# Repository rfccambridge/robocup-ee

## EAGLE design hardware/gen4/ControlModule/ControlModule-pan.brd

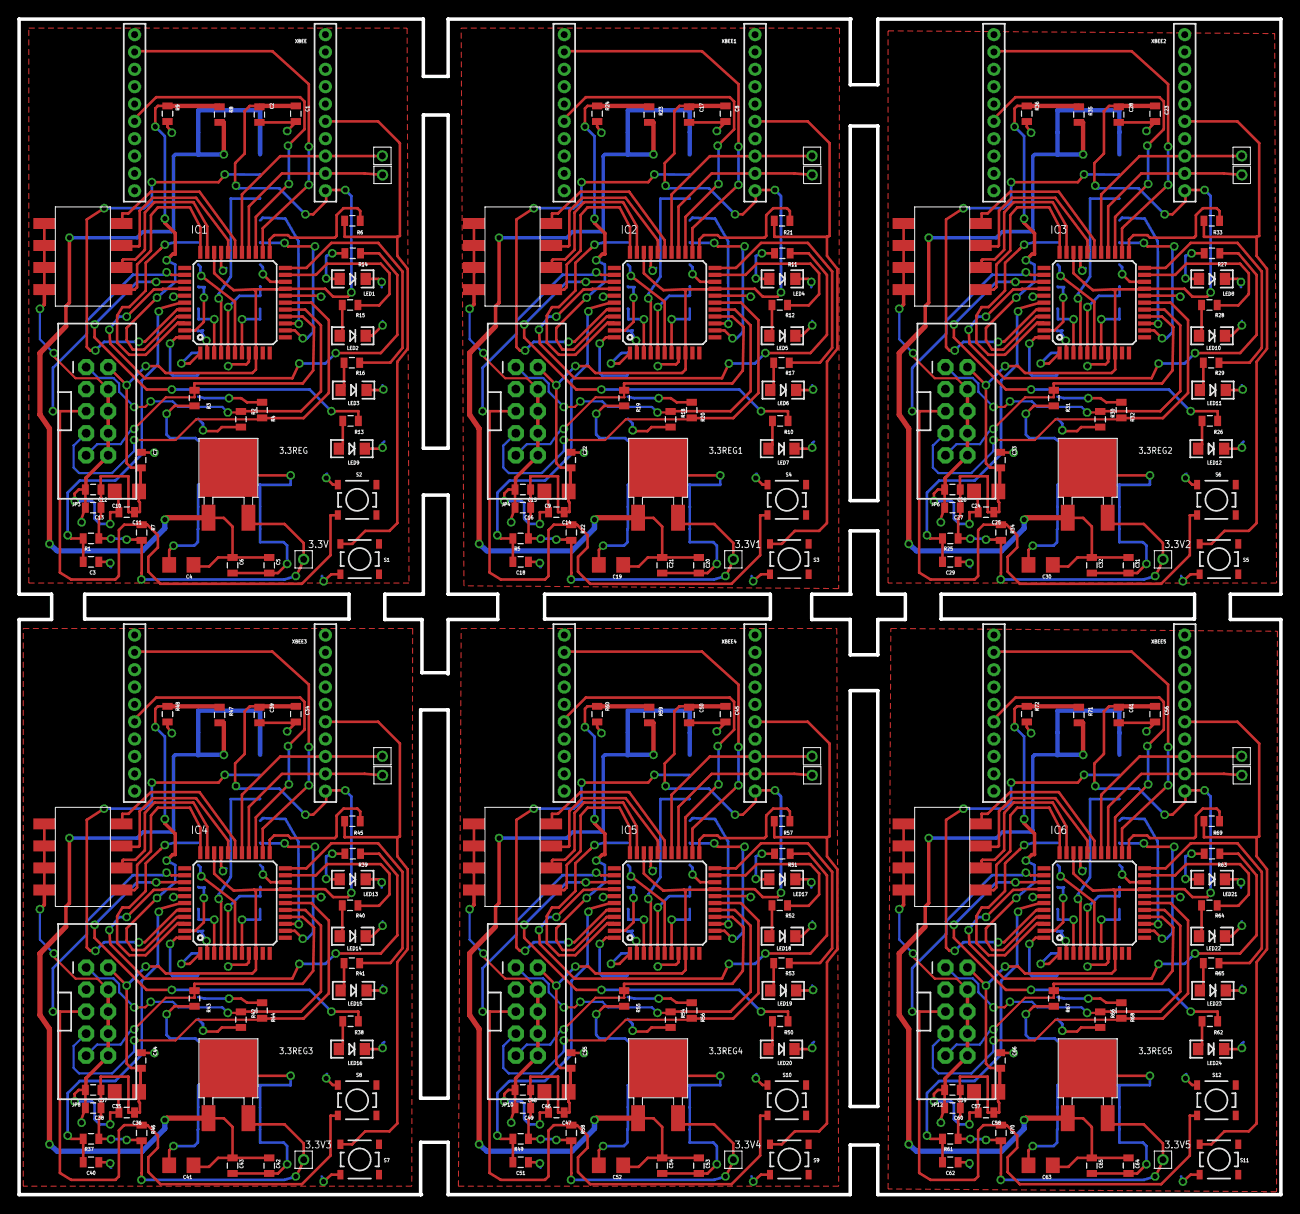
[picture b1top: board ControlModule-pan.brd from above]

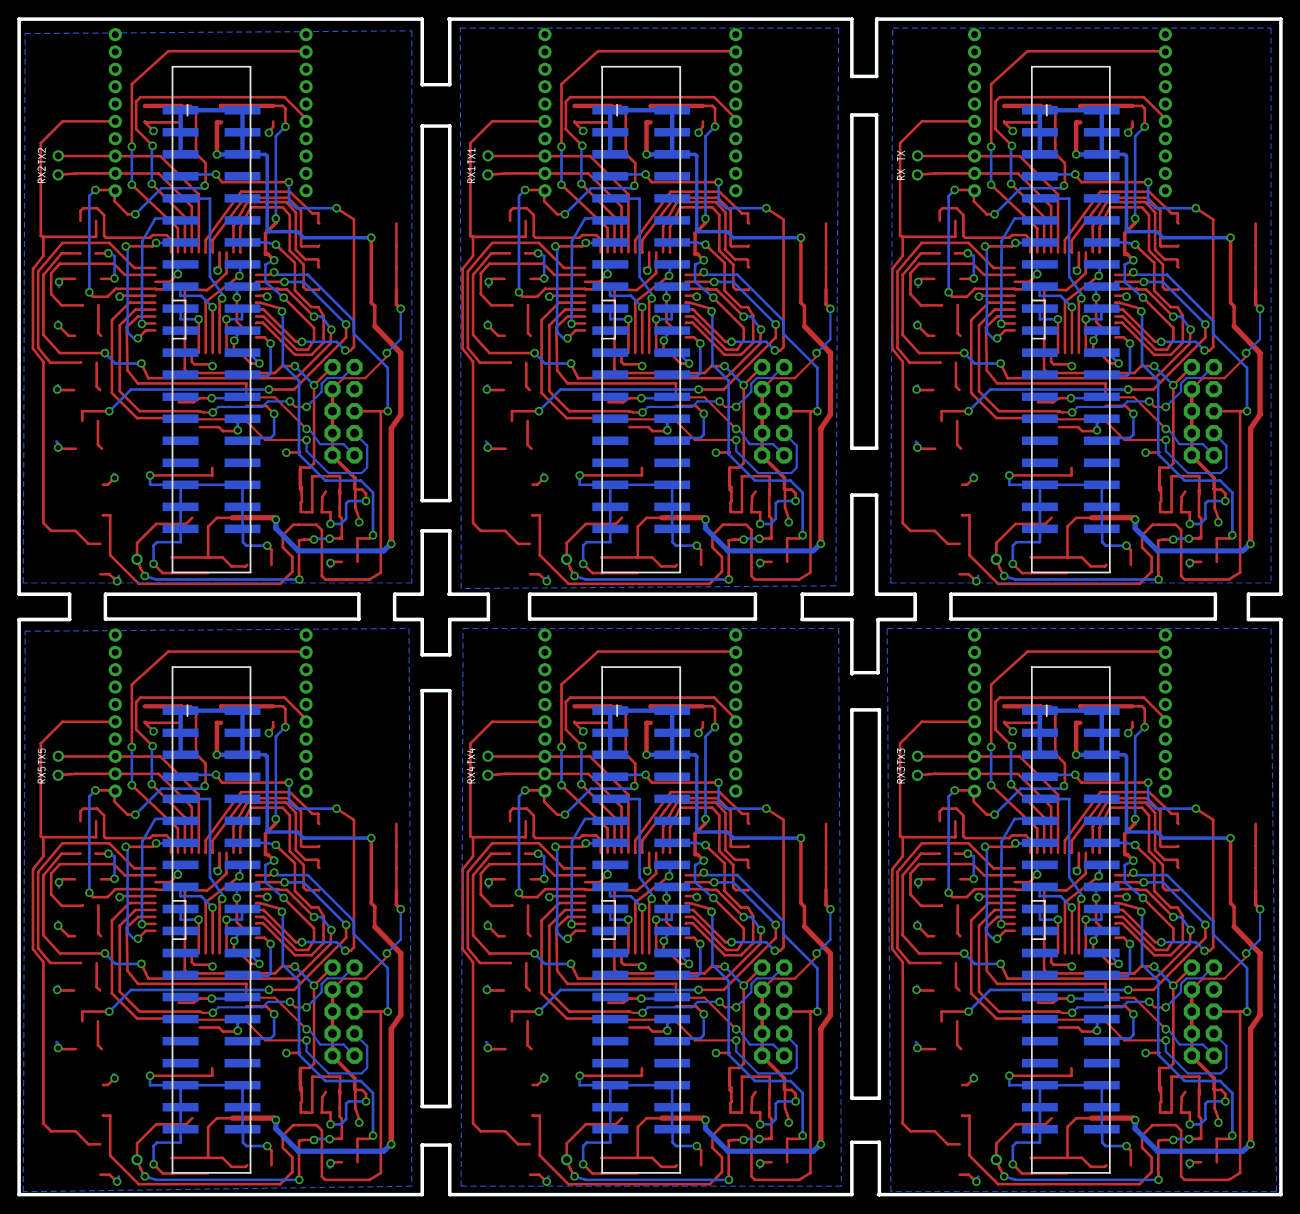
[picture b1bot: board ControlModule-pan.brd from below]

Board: 2 copper layers, 145.5 x 135.5 mm, 229 parts (6 on the bottom side), 270 nets.

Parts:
3.3REG, 3.3REG1, 3.3REG2, 3.3REG3, 3.3REG4, 3.3REG5: 3.3REG1AREG; DPAK
3.3V, 3.3V1, 3.3V2, 3.3V3, 3.3V4, 3.3V5: TEST_PT; TESTING_PT
C1, C5, C8, C12, C13, C15, C16, C20, C23, C26, C27, C31, C34, C37, C38, C42, C45, C48, C49, C53, C56, C59, C60, C64: 1uF; 0805
C2, C17, C28, C39, C50, C61: 0.01uF; 0805
C3, C18, C29, C40, C51, C62: 0.1uF; 0805
C4, C9, C10, C19, C24, C30, C35, C41, C46, C52, C57, C63: 47uF; 1206
C6, C7, C11, C14, C21, C22, C25, C32, C33, C36, C43, C44, C47, C54, C55, C58, C65, C66: .01uF; 0805
FRAME1: FRAME-LETTER; CREATIVE_COMMONS
IC1, IC2, IC3, IC4, IC5, IC6: XMEGA16A4A; TQFP44
JP1, JP2, JP5, JP7, JP9, JP11: M20X2SHROUDED_SMT; 2X20_SHROUDED_SMT
JP3, JP4, JP6, JP8, JP10, JP12: 2X5-SHROUDED
LED1, LED2, LED3, LED4, LED5, LED6, LED7, LED8, LED9, LED10, LED11, LED12, LED13, LED14, LED15, LED16, LED17, LED18, LED19, LED20, LED21, LED22, LED23, LED24: LED-1206
R1, R5, R7, R22, R25, R34, R37, R46, R49, R58, R61, R70: 10k; 0805
R2, R3, R4, R6, R18, R19, R20, R21, R30, R31, R32, R33, R42, R43, R44, R45, R54, R55, R56, R57, R66, R67, R68, R69: 4.7k; 0805
R8, R23, R35, R47, R59, R71: 80k; 0805
R9, R24, R36, R48, R60, R72: 20k; 0805
R10, R11, R12, R13, R14, R15, R16, R17, R26, R27, R28, R29, R38, R39, R40, R41, R50, R51, R52, R53, R62, R63, R64, R65: 1k; 0805
RX, RX1, RX2, RX3, RX4, RX5: TEST_PT; TESTING_PT
S1, S2, S3, S4, S5, S6, S7, S8, S9, S10, S11, S12: SWITCH-MOMENTARY-2SMD-2; TACTILE_SWITCH_SMD-2
TX, TX1, TX2, TX3, TX4, TX5: TEST_PT; TESTING_PT
U$1, U$2, U$3, U$4, U$5, U$6: 4-POS-DIP; 4-POS-DIP-SMD
XBEE, XBEE1, XBEE2, XBEE3, XBEE4, XBEE5: XBEE-1B1; XBEE-1

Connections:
3.3V: 3.3REG.SOURCE, 3.3V.P$1, C1.1, C2.1, C7.1, C10.1, C11.2, C12.2, C13.1, IC1.9, IC1.19, IC1.31, JP3.2, R1.2, R7.2, XBEE.1
3.3V1: 3.3REG1.SOURCE, 3.3V1.P$1, C8.1, C9.1, C14.2, C15.2, C16.1, C17.1, C22.1, IC2.9, IC2.19, IC2.31, JP4.2, R5.2, R22.2, XBEE1.1
3.3V2: 3.3REG2.SOURCE, 3.3V2.P$1, C23.1, C24.1, C25.2, C26.2, C27.1, C28.1, C33.1, IC3.9, IC3.19, IC3.31, JP6.2, R25.2, R34.2, XBEE2.1
3.3V3: 3.3REG3.SOURCE, 3.3V3.P$1, C34.1, C35.1, C36.2, C37.2, C38.1, C39.1, C44.1, IC4.9, IC4.19, IC4.31, JP8.2, R37.2, R46.2, XBEE3.1
3.3V4: 3.3REG4.SOURCE, 3.3V4.P$1, C45.1, C46.1, C47.2, C48.2, C49.1, C50.1, C55.1, IC5.9, IC5.19, IC5.31, JP10.2, R49.2, R58.2, XBEE4.1
3.3V5: 3.3REG5.SOURCE, 3.3V5.P$1, C56.1, C57.1, C58.2, C59.2, C60.1, C61.1, C66.1, IC6.9, IC6.19, IC6.31, JP12.2, R61.2, R70.2, XBEE5.1
12V: 3.3REG.GATE, C4.1, C5.1, C6.1, JP1.1, JP1.2, JP1.3, JP1.4, JP1.5, JP1.6, R8.2
12V1: 3.3REG1.GATE, C19.1, C20.1, C21.1, JP2.1, JP2.2, JP2.3, JP2.4, JP2.5, JP2.6, R23.2
12V2: 3.3REG2.GATE, C30.1, C31.1, C32.1, JP5.1, JP5.2, JP5.3, JP5.4, JP5.5, JP5.6, R35.2
12V3: 3.3REG3.GATE, C41.1, C42.1, C43.1, JP7.1, JP7.2, JP7.3, JP7.4, JP7.5, JP7.6, R47.2
12V4: 3.3REG4.GATE, C52.1, C53.1, C54.1, JP9.1, JP9.2, JP9.3, JP9.4, JP9.5, JP9.6, R59.2
12V5: 3.3REG5.GATE, C63.1, C64.1, C65.1, JP11.1, JP11.2, JP11.3, JP11.4, JP11.5, JP11.6, R71.2
12VGND: 3.3REG.DRAIN, C4.2, C5.2, C6.2, JP1.35, JP1.36, JP1.37, JP1.38, JP1.39, JP1.40
12VGND1: 3.3REG1.DRAIN, C19.2, C20.2, C21.2, JP2.35, JP2.36, JP2.37, JP2.38, JP2.39, JP2.40
12VGND2: 3.3REG2.DRAIN, C30.2, C31.2, C32.2, JP5.35, JP5.36, JP5.37, JP5.38, JP5.39, JP5.40
12VGND3: 3.3REG3.DRAIN, C41.2, C42.2, C43.2, JP7.35, JP7.36, JP7.37, JP7.38, JP7.39, JP7.40
12VGND4: 3.3REG4.DRAIN, C52.2, C53.2, C54.2, JP9.35, JP9.36, JP9.37, JP9.38, JP9.39, JP9.40
12VGND5: 3.3REG5.DRAIN, C63.2, C64.2, C65.2, JP11.35, JP11.36, JP11.37, JP11.38, JP11.39, JP11.40
BATSENSE: IC1.41, R8.1, R9.2
BATSENSE1: IC2.41, R23.1, R24.2
BATSENSE2: IC3.41, R35.1, R36.2
BATSENSE3: IC4.41, R47.1, R48.2
BATSENSE4: IC5.41, R59.1, R60.2
BATSENSE5: IC6.41, R71.1, R72.2
BB_IN: IC1.40, JP1.7
BB_IN1: IC2.40, JP2.7
BB_IN2: IC3.40, JP5.7
BB_IN3: IC4.40, JP7.7
BB_IN4: IC5.40, JP9.7
BB_IN5: IC6.40, JP11.7
BB_OUT: IC1.4, JP1.9
BB_OUT1: IC2.4, JP2.9
BB_OUT2: IC3.4, JP5.9
BB_OUT3: IC4.4, JP7.9
BB_OUT4: IC5.4, JP9.9
BB_OUT5: IC6.4, JP11.9
BID0: IC1.28, U$1.1
BID1: IC1.29, U$1.2
BID2: IC1.32, U$1.3
BID3: IC1.33, U$1.4
BID4: IC2.28, U$2.1
BID5: IC2.32, U$2.3
BID6: IC2.29, U$2.2
BID7: IC2.33, U$2.4
BID8: IC3.28, U$3.1
BID9: IC3.32, U$3.3
BID10: IC3.29, U$3.2
BID11: IC3.33, U$3.4
BID12: IC4.28, U$4.1
BID13: IC4.32, U$4.3
BID14: IC4.29, U$4.2
BID15: IC4.33, U$4.4
BID16: IC5.28, U$5.1
BID17: IC5.32, U$5.3
BID18: IC5.29, U$5.2
BID19: IC5.33, U$5.4
BID20: IC6.28, U$6.1
BID21: IC6.32, U$6.3
BID22: IC6.29, U$6.2
BID23: IC6.33, U$6.4
CHARGE: IC1.7, JP1.19
CHARGE1: IC2.7, JP2.19
CHARGE2: IC3.7, JP5.19
CHARGE3: IC4.7, JP7.19
CHARGE4: IC5.7, JP9.19
CHARGE5: IC6.7, JP11.19
CHARGE_DONE: IC1.5, JP1.17
CHARGE_DONE1: IC2.5, JP2.17
CHARGE_DONE2: IC3.5, JP5.17
CHARGE_DONE3: IC4.5, JP7.17
CHARGE_DONE4: IC5.5, JP9.17
CHARGE_DONE5: IC6.5, JP11.17
CHIP_ENABLE: IC1.13, JP1.13
CHIP_ENABLE1: IC2.13, JP2.13
CHIP_ENABLE2: IC3.13, JP5.13
CHIP_ENABLE3: IC4.13, JP7.13
CHIP_ENABLE4: IC5.13, JP9.13
CHIP_ENABLE5: IC6.13, JP11.13
CTS: IC1.24, XBEE.12
CTS1: IC2.24, XBEE1.12
CTS2: IC3.24, XBEE2.12
CTS3: IC4.24, XBEE3.12
CTS4: IC5.24, XBEE4.12
CTS5: IC6.24, XBEE5.12
DISCHARGE: IC1.6, JP1.16
DISCHARGE1: IC2.6, JP2.16
DISCHARGE2: IC3.6, JP5.16
DISCHARGE3: IC4.6, JP7.16
DISCHARGE4: IC5.6, JP9.16
DISCHARGE5: IC6.6, JP11.16
DIVCAP: IC1.42, JP1.14
DIVCAP1: IC2.42, JP2.14
DIVCAP2: IC3.42, JP5.14
DIVCAP3: IC4.42, JP7.14
DIVCAP4: IC5.42, JP9.14
DIVCAP5: IC6.42, JP11.14
DRIB: IC1.43, JP1.18
DRIB1: IC2.43, JP2.18
DRIB2: IC3.43, JP5.18
DRIB3: IC4.43, JP7.18
DRIB4: IC5.43, JP9.18
DRIB5: IC6.43, JP11.18
GLED1: IC1.36, R13.2
GLED2: IC1.21, R15.2
GLED3: IC2.36, R10.2
GLED4: IC2.21, R12.2
GLED5: IC3.36, R26.2
GLED6: IC3.21, R28.2
GLED7: IC4.36, R38.2
GLED8: IC4.21, R40.2
GLED9: IC5.36, R50.2
GLED10: IC5.21, R52.2
GLED11: IC6.36, R62.2
GLED12: IC6.21, R64.2
GND: C1.2, C2.2, C3.1, C7.2, C10.2, C11.1, C12.1, C13.2, IC1.8, IC1.18, IC1.30, IC1.38, JP1.33, JP1.34, JP3.4, JP3.6, JP3.8, JP3.10, LED1.C, LED2.C, LED3.C, LED9.C, R9.1, S1.1, S2.2, U$1.5, U$1.6, U$1.7, U$1.8, XBEE.10
GND1: C8.2, C9.2, C14.1, C15.1, C16.2, C17.2, C18.1, C22.2, IC2.8, IC2.18, IC2.30, IC2.38, JP2.33, JP2.34, JP4.4, JP4.6, JP4.8, JP4.10, LED4.C, LED5.C, LED6.C, LED7.C, R24.1, S3.1, S4.2, U$2.5, U$2.6, U$2.7, U$2.8, XBEE1.10
GND2: C23.2, C24.2, C25.1, C26.1, C27.2, C28.2, C29.1, C33.2, IC3.8, IC3.18, IC3.30, IC3.38, JP5.33, JP5.34, JP6.4, JP6.6, JP6.8, JP6.10, LED8.C, LED10.C, LED11.C, LED12.C, R36.1, S5.1, S6.2, U$3.5, U$3.6, U$3.7, U$3.8, XBEE2.10
GND3: C34.2, C35.2, C36.1, C37.1, C38.2, C39.2, C40.1, C44.2, IC4.8, IC4.18, IC4.30, IC4.38, JP7.33, JP7.34, JP8.4, JP8.6, JP8.8, JP8.10, LED13.C, LED14.C, LED15.C, LED16.C, R48.1, S7.1, S8.2, U$4.5, U$4.6, U$4.7, U$4.8, XBEE3.10
GND4: C45.2, C46.2, C47.1, C48.1, C49.2, C50.2, C51.1, C55.2, IC5.8, IC5.18, IC5.30, IC5.38, JP9.33, JP9.34, JP10.4, JP10.6, JP10.8, JP10.10, LED17.C, LED18.C, LED19.C, LED20.C, R60.1, S9.1, S10.2, U$5.5, U$5.6, U$5.7, U$5.8, XBEE4.10
GND5: C56.2, C57.2, C58.1, C59.1, C60.2, C61.2, C62.1, C66.2, IC6.8, IC6.18, IC6.30, IC6.38, JP11.33, JP11.34, JP12.4, JP12.6, JP12.8, JP12.10, LED21.C, LED22.C, LED23.C, LED24.C, R72.1, S11.1, S12.2, U$6.5, U$6.6, U$6.7, U$6.8, XBEE5.10
KICK_ENABLE: IC1.14, JP1.11
KICK_ENABLE1: IC2.14, JP2.11
KICK_ENABLE2: IC3.14, JP5.11
KICK_ENABLE3: IC4.14, JP7.11
KICK_ENABLE4: IC5.14, JP9.11
KICK_ENABLE5: IC6.14, JP11.11
KICK_REF: IC1.20, JP1.15
KICK_REF1: IC2.20, JP2.15
KICK_REF2: IC3.20, JP5.15
KICK_REF3: IC4.20, JP7.15
KICK_REF4: IC5.20, JP9.15
KICK_REF5: IC6.20, JP11.15
MISO: IC1.15, JP3.9, R3.1
MISO1: IC2.15, JP4.9, R19.1
MISO2: IC3.15, JP6.9, R31.1
MISO3: IC4.15, JP8.9, R43.1
MISO4: IC5.15, JP10.9, R55.1
MISO5: IC6.15, JP12.9, R67.1
MOSI: IC1.16, JP3.1, R2.1
MOSI1: IC2.16, JP4.1, R18.1
MOSI2: IC3.16, JP6.1, R30.1
MOSI3: IC4.16, JP8.1, R42.1
MOSI4: IC5.16, JP10.1, R54.1
MOSI5: IC6.16, JP12.1, R66.1
unnamed: C3.2, IC1.39, R1.1
unnamed: LED9.A, R13.1
unnamed: C18.2, IC2.39, R5.1
unnamed: IC2.23, R21.1
unnamed: IC1.23, R6.1
unnamed: JP1.30, R2.2
unnamed: JP1.32, R3.2
unnamed: JP1.28, R4.2
unnamed: LED1.A, R14.1
unnamed: LED2.A, R15.1
unnamed: LED3.A, R16.1
unnamed: JP2.30, R18.2
unnamed: JP2.32, R19.2
unnamed: JP2.28, R20.2
unnamed: LED7.A, R10.1
unnamed: LED4.A, R11.1
unnamed: LED5.A, R12.1
unnamed: LED6.A, R17.1
unnamed: C29.2, IC3.39, R25.1
unnamed: IC3.23, R33.1
unnamed: JP5.30, R30.2
unnamed: JP5.32, R31.2
unnamed: JP5.28, R32.2
unnamed: LED12.A, R26.1
unnamed: LED8.A, R27.1
unnamed: LED10.A, R28.1
unnamed: LED11.A, R29.1
unnamed: C40.2, IC4.39, R37.1
unnamed: IC4.23, R45.1
unnamed: JP7.30, R42.2
unnamed: JP7.32, R43.2
unnamed: JP7.28, R44.2
unnamed: LED16.A, R38.1
unnamed: LED13.A, R39.1
unnamed: LED14.A, R40.1
unnamed: LED15.A, R41.1
unnamed: C51.2, IC5.39, R49.1
unnamed: IC5.23, R57.1
unnamed: JP9.30, R54.2
unnamed: JP9.32, R55.2
unnamed: JP9.28, R56.2
unnamed: LED20.A, R50.1
unnamed: LED17.A, R51.1
unnamed: LED18.A, R52.1
unnamed: LED19.A, R53.1
unnamed: C62.2, IC6.39, R61.1
unnamed: IC6.23, R69.1
unnamed: JP11.30, R66.2
unnamed: JP11.32, R67.2
unnamed: JP11.28, R68.2
unnamed: LED24.A, R62.1
unnamed: LED21.A, R63.1
unnamed: LED22.A, R64.1
unnamed: LED23.A, R65.1
RESET: IC1.35, JP3.5, R7.1, S2.1
RESET1: IC2.35, JP4.5, R22.1, S4.1
RESET2: IC3.35, JP6.5, R34.1, S6.1
RESET3: IC4.35, JP8.5, R46.1, S8.1
RESET4: IC5.35, JP10.5, R58.1, S10.1
RESET5: IC6.35, JP12.5, R70.1, S12.1
RLED1: IC1.37, R14.2
RLED2: IC1.22, R16.2
RLED3: IC2.37, R11.2
RLED4: IC2.22, R17.2
RLED5: IC3.37, R27.2
RLED6: IC3.22, R29.2
RLED7: IC4.37, R39.2
RLED8: IC4.22, R41.2
RLED9: IC5.37, R51.2
RLED10: IC5.22, R53.2
RLED11: IC6.37, R63.2
RLED12: IC6.22, R65.2
RTS: IC1.25, XBEE.16
RTS1: IC2.25, XBEE1.16
RTS2: IC3.25, XBEE2.16
RTS3: IC4.25, XBEE3.16
RTS4: IC5.25, XBEE4.16
RTS5: IC6.25, XBEE5.16
RX: IC1.26, RX.P$1, XBEE.2
RX1: IC2.26, RX1.P$1, XBEE1.2
RX2: IC3.26, RX2.P$1, XBEE2.2
RX3: IC4.26, RX3.P$1, XBEE3.2
RX4: IC5.26, RX4.P$1, XBEE4.2
RX5: IC6.26, RX5.P$1, XBEE5.2
SCK: IC1.17, JP3.7, R4.1
SCK1: IC2.17, JP4.7, R20.1
SCK2: IC3.17, JP6.7, R32.1
SCK3: IC4.17, JP8.7, R44.1
SCK4: IC5.17, JP10.7, R56.1
SCK5: IC6.17, JP12.7, R68.1
SS_1: IC1.3, JP1.20
SS_2: IC1.2, JP1.22
SS_3: IC1.1, JP1.24
SS_4: IC1.44, JP1.26
SS_5: IC2.3, JP2.20
SS_6: IC2.2, JP2.22
SS_7: IC2.1, JP2.24
SS_8: IC2.44, JP2.26
SS_9: IC3.3, JP5.20
SS_10: IC3.2, JP5.22
SS_11: IC3.1, JP5.24
SS_12: IC3.44, JP5.26
SS_13: IC4.3, JP7.20
SS_14: IC4.2, JP7.22
SS_15: IC4.1, JP7.24
SS_16: IC4.44, JP7.26
SS_17: IC5.3, JP9.20
SS_18: IC5.2, JP9.22
SS_19: IC5.1, JP9.24
SS_20: IC5.44, JP9.26
SS_21: IC6.3, JP11.20
SS_22: IC6.2, JP11.22
SS_23: IC6.1, JP11.24
SS_24: IC6.44, JP11.26
TX: IC1.27, TX.P$1, XBEE.3
TX1: IC2.27, TX1.P$1, XBEE1.3
TX2: IC3.27, TX2.P$1, XBEE2.3
TX3: IC4.27, TX3.P$1, XBEE3.3
TX4: IC5.27, TX4.P$1, XBEE4.3
TX5: IC6.27, TX5.P$1, XBEE5.3
XBRST: R6.2, S1.2, XBEE.5
XBRST1: R21.2, S3.2, XBEE1.5
XBRST2: R33.2, S5.2, XBEE2.5
XBRST3: R45.2, S7.2, XBEE3.5
XBRST4: R57.2, S9.2, XBEE4.5
XBRST5: R69.2, S11.2, XBEE5.5

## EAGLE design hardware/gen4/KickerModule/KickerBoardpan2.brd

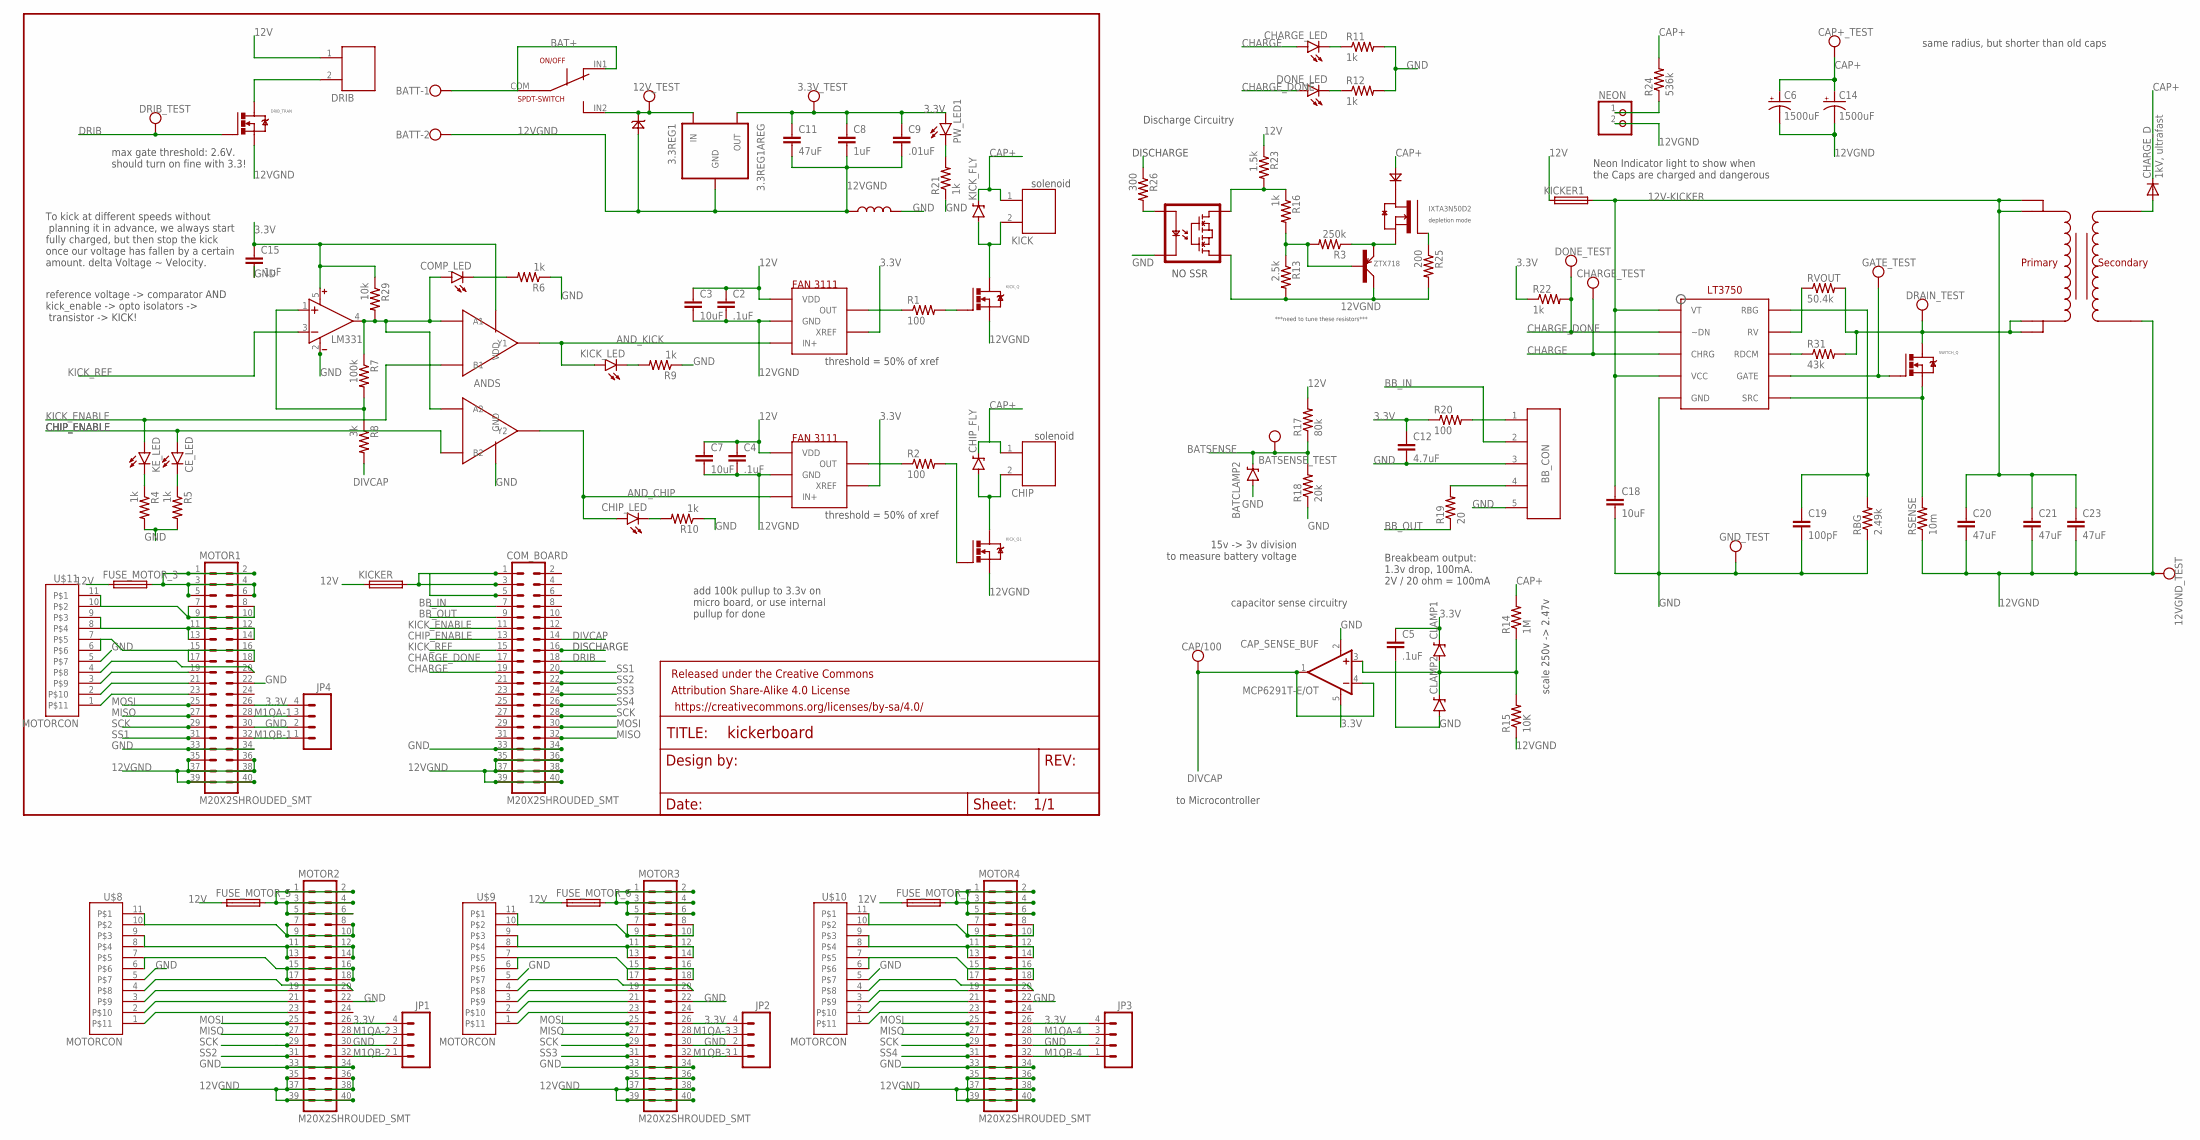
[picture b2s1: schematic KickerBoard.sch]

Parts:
3.3REG1: 3.3REG1AREG; DPAK
3.3V_TEST, 12VGND_TEST, 12V_TEST: TEST_PT; TESTING_PT
ANDS: AND-DUAL; TSSOP8
BATCLAMP2: DIODE-ZENERDO214AC; DO214AC
BATSENSE_TEST: TEST_PT; TESTING_PT
BATT: W237-102
BB_CON: JST-5; JST-5-2MM
C2, C4: .1uF; 1206
C3, C7: 10uF; 1206
C5, C15: .1uF; 0805
C6, C14: 1500uF; EB35D
C8: 1uF; 0805
C9: .01uF; 0805
C11, C20, C21, C23: 47uF; 1206
C12: 4.7uF; 0805
C18: 10uF; 0805
C19: 100pF; 0805
CAP+_TEST: TEST_PT; TESTING_PT
CAP/100: TEST_PT; TESTING_PT
CAP_COMP: LM331; SOT23-5
CAP_SENSE_BUF: MCP6291T-E/OT; SOT23-5
CE_LED: LED1206; LED-1206
CHARGE_D: 1kV, ultrafast; DO214AC
CHARGE_LED: LED1206; LED-1206
CHARGE_TEST: TEST_PT; TESTING_PT
CHARGE_U: LT3750; 10-MSOP
CHIP: JST-22MM; JST-2-2MM
CHIP_FLY: DIODE-ZENERDO214AB; DO214AB
CHIP_LED: LED1206; LED-1206
CLAMP1, CLAMP2: DIODE-ZENERDO214AC; DO214AC
COMP_LED: LED1206; LED-1206
COM_BOARD: M20X2SHROUDED_SMT; 2X20_SHROUDED_SMT
DONE_LED: LED1206; LED-1206
DONE_TEST: TEST_PT; TESTING_PT
DRAIN_TEST: TEST_PT; TESTING_PT
DRIB: JST-22MM; JST-2-2MM
DRIB_TEST: TEST_PT; TESTING_PT
DRIB_TRAN: N-MOSFETDPAK; DPAK
FRAME4: FRAME-LETTER; CREATIVE_COMMONS
FUSE_MOTOR_3, FUSE_MOTOR_5, FUSE_MOTOR_6, FUSE_MOTOR_7: TR5
GATE_TEST: TEST_PT; TESTING_PT
GND_TEST: TEST_PT; TESTING_PT
JP1, JP2, JP3, JP4: M04SMD_RA_FEMALE; 1X04_SMD_RA_FEMALE
KE_LED: LED1206; LED-1206
KICK: JST-22MM; JST-2-2MM
KICKER, KICKER1: TR5
KICK_FLY: DIODE-ZENERDO214AB; DO214AB
KICK_LED: LED1206; LED-1206
KICK_Q, KICK_Q1: N-MOSFETDPAK; DPAK
MOTOR1, MOTOR2, MOTOR3, MOTOR4: M20X2SHROUDED_SMT; 2X20_SHROUDED_SMT
NEON: PINHD-1X2; 1X02
ON/OFF: SPDT-SWITCH; CK_SWITCH
PW_LED1: LED1206; LED-1206
R1, R2, R20: 100; 0805
R3: 250k; 0805
R4, R5, R6, R9, R10, R11, R12, R16, R21, R22: 1k; 0805
R7: 100k; 0805
R8: 3k; 0805
R13: 2.5k; 0805
R14: 1M; 0805
R15: 10K; 0805
R17: 80k; 0805
R18: 20k; 0805
R19: 20; 0805
R23: 1.5k; 0805
R24: 536k; 0805
R25: 200; 0805
R26: 300; 0805
R29: 10k; 0805
R31: 43k; 0805
RBG: 2.49k; 0805
RSENSE: 10m; R2512
RVOUT: 50.4k; 0805
SWITCH_Q: N-MOSFETDPAK; DPAK
U$1, U$4: FAN31111; SOT23-5
U$2: IXTA3N50D2; TO-263
U$3: 32052-TRANSFORMER; 10-TRANSFORMER
U$5: VO1400AEFTR; SOP4
U$6: ZTX718; TO92
U$7: 1N4007; THROUGH-HOLE-2
U$8, U$9, U$10, U$11: MOTORCON; GEN3CON
U$12: 13VZENER; THROUGH-HOLE-2
U$13: INDUCTOR; 0805

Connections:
3.3V: 3.3REG1.SOURCE (OUT), 3.3V_TEST.P$1, ANDS.P$8 (VDD), C5.1, C8.1, C9.1, C11.1, C12.1, C15.1, CAP_COMP.5 (V+), CAP_SENSE_BUF.5 (V+), CLAMP1.C, JP1.4, JP2.4, JP3.4, JP4.4, MOTOR1.26, MOTOR2.26, MOTOR3.26, MOTOR4.26, PW_LED1.A, R20.1, R22.1, R29.1, U$1.4 (XREF), U$4.4 (XREF)
12V: 3.3REG1.GATE (IN), 12V_TEST.P$1, C2.1, C3.1, C4.1, C7.1, DRIB.1, FUSE_MOTOR_3.1, FUSE_MOTOR_5.1, FUSE_MOTOR_6.1, FUSE_MOTOR_7.1, KICKER.1, KICKER1.1, ON/OFF.IN2 (P2), R17.2, R23.1, U$1.1 (VDD), U$4.1 (VDD), U$12.-
12V-KICKER: C18.1, C20.1, C21.1, C23.1, CHARGE_U.P$1 (VT), CHARGE_U.P$4 (VCC), KICKER1.2, U$3.P$4, U$3.P$5
12VGND: 3.3REG1.DRAIN (GND), 12VGND_TEST.P$1, BATT.2, C2.2, C3.2, C4.2, C6.-, C7.2, C8.2, C9.2, C11.2, C14.-, C20.2, C21.2, C23.2, COM_BOARD.35, COM_BOARD.36, COM_BOARD.37, COM_BOARD.38, COM_BOARD.39, COM_BOARD.40, DRIB_TRAN.SOURCE (S), KICK_Q.SOURCE (S), KICK_Q1.SOURCE (S), MOTOR1.35, MOTOR1.36, MOTOR1.37, MOTOR1.38, MOTOR1.39, MOTOR1.40, MOTOR2.35, MOTOR2.36, MOTOR2.37, MOTOR2.38, MOTOR2.39, MOTOR2.40, MOTOR3.35, MOTOR3.36, MOTOR3.37, MOTOR3.38, MOTOR3.39, MOTOR3.40, MOTOR4.35, MOTOR4.36, MOTOR4.37, MOTOR4.38, MOTOR4.39, MOTOR4.40, NEON.2, R13.2, R15.1, R25.2, RSENSE.1, U$1.2 (GND), U$3.P$10, U$4.2 (GND), U$5.3 (S2), U$6.LEFT (COLLECTOR), U$12.+, U$13.1
AND_CHIP: ANDS.P$3 (Y2), CHIP_LED.A, U$1.3 (IN+)
AND_KICK: ANDS.P$7 (Y1), KICK_LED.A, U$4.3 (IN+)
BAT+: BATT.1, ON/OFF.COM, ON/OFF.IN1 (P1)
BATSENSE: BATCLAMP2.C, BATSENSE_TEST.P$1, R17.1, R18.2
BB_IN: BB_CON.2, COM_BOARD.7
BB_OUT: COM_BOARD.9, R19.1
CAP+: C6.+, C14.+, CAP+_TEST.P$1, CHARGE_D.C, CHIP.1, CHIP_FLY.CATHODE (C), KICK.1, KICK_FLY.CATHODE (C), R14.2, R24.2, U$7.+ (D+)
CHARGE: CHARGE_LED.A, CHARGE_TEST.P$1, CHARGE_U.P$3 (CHRG), COM_BOARD.19
CHARGE_DONE: CHARGE_U.P$2 (~DN), COM_BOARD.17, DONE_LED.A, DONE_TEST.P$1, R22.2
CHIP_ENABLE: ANDS.P$6 (B2), CE_LED.A, COM_BOARD.13
COMP_OUT: ANDS.P$1 (A1), ANDS.P$5 (A2), CAP_COMP.4 (OUT), COMP_LED.A, R7.1, R29.2
DISCHARGE: COM_BOARD.16, R26.1
DIVCAP: CAP/100.P$1, CAP_SENSE_BUF.1 (OUT), CAP_SENSE_BUF.4 (-IN), COM_BOARD.14, R8.2
DRIB: COM_BOARD.18, DRIB_TEST.P$1, DRIB_TRAN.GATE (G)
GND: ANDS.P$4 (GND), BATCLAMP2.A, BB_CON.3, BB_CON.5, C5.2, C12.2, C15.2, C18.2, C19.2, CAP_COMP.2 (V-), CAP_SENSE_BUF.2 (V-), CHARGE_U.P$5 (GND), CLAMP2.A, COM_BOARD.33, COM_BOARD.34, GND_TEST.P$1, JP1.2, JP2.2, JP3.2, JP4.2, MOTOR1.22, MOTOR1.30, MOTOR1.33, MOTOR1.34, MOTOR2.22, MOTOR2.30, MOTOR2.33, MOTOR2.34, MOTOR3.22, MOTOR3.30, MOTOR3.33, MOTOR3.34, MOTOR4.22, MOTOR4.30, MOTOR4.33, MOTOR4.34, R4.2, R5.2, R6.1, R9.1, R10.1, R11.2, R12.2, R18.1, R21.1, RBG.1, U$5.2 (LED-), U$8.5, U$9.5, U$10.5, U$11.5, U$13.2
HYSTERESIS: CAP_COMP.1 (IN+), R7.2, R8.1
KICK_ENABLE: ANDS.P$2 (B1), COM_BOARD.11, KE_LED.A
KICK_REF: CAP_COMP.3 (IN-), COM_BOARD.15
LOWCHIP: CHIP.2, CHIP_FLY.ANODE (A), KICK_Q1.DRAIN (D)
LOWKICK: KICK.2, KICK_FLY.ANODE (A), KICK_Q.DRAIN (D)
M1QA-1: JP4.3, MOTOR1.28
M1QA-2: JP1.3, MOTOR2.28
M1QA-3: JP2.3, MOTOR3.28
M1QA-4: JP3.3, MOTOR4.28
M1QB-1: JP4.1, MOTOR1.32
M1QB-2: JP1.1, MOTOR2.32
M1QB-3: JP2.1, MOTOR3.32
M1QB-4: JP3.1, MOTOR4.32
MISO: COM_BOARD.32, MOTOR1.27, MOTOR2.27, MOTOR3.27, MOTOR4.27
MOSI: COM_BOARD.30, MOTOR1.25, MOTOR2.25, MOTOR3.25, MOTOR4.25
unnamed: DRAIN_TEST.P$1, R31.2, RVOUT.2, SWITCH_Q.DRAIN (D), U$3.P$6, U$3.P$7
unnamed: R1.1, U$4.5 (OUT)
unnamed: KICK_Q1.GATE (G), R2.2
unnamed: FUSE_MOTOR_6.2, MOTOR3.1, MOTOR3.2, MOTOR3.3, MOTOR3.4, MOTOR3.5, MOTOR3.6
unnamed: R2.1, U$1.5 (OUT)
unnamed: CHARGE_U.P$8 (RDCM), R31.1
unnamed: C19.1, CHARGE_U.P$10 (RBG), RBG.2
unnamed: KICK_Q.GATE (G), R1.2
unnamed: CHARGE_U.P$7 (GATE), GATE_TEST.P$1, SWITCH_Q.GATE (G)
unnamed: R3.1, U$2.LOWER_RIGHT (SOURCE), U$6.RIGHT (EMITTER)
unnamed: KE_LED.C, R4.1
unnamed: CHARGE_U.P$9 (RV), RVOUT.1
unnamed: CE_LED.C, R5.1
unnamed: COMP_LED.C, R6.2
unnamed: KICK_LED.C, R9.2
unnamed: CHIP_LED.C, R10.2
unnamed: R3.2, R13.1, R16.2, U$6.CENTER (BASE)
unnamed: DONE_LED.C, R12.1
unnamed: CHARGE_LED.C, R11.1
unnamed: R25.1, U$2.LOWER_LEFT (GATE)
unnamed: PW_LED1.C, R21.2
unnamed: CHARGE_U.P$6 (SRC), RSENSE.2, SWITCH_Q.SOURCE (S)
unnamed: FUSE_MOTOR_7.2, MOTOR4.1, MOTOR4.2, MOTOR4.3, MOTOR4.4, MOTOR4.5, MOTOR4.6
unnamed: FUSE_MOTOR_5.2, MOTOR2.1, MOTOR2.2, MOTOR2.3, MOTOR2.4, MOTOR2.5, MOTOR2.6
unnamed: FUSE_MOTOR_3.2, MOTOR1.1, MOTOR1.2, MOTOR1.3, MOTOR1.4, MOTOR1.5, MOTOR1.6
unnamed: COM_BOARD.1, COM_BOARD.3, COM_BOARD.5, KICKER.2
unnamed: R16.1, R23.2, U$5.4 (S1)
unnamed: R26.2, U$5.1 (LED+)
unnamed: BB_CON.4, R19.2
unnamed: U$2.TAB (DRAIN), U$7.- (D-)
unnamed: MOTOR2.7, MOTOR2.8, MOTOR2.9, MOTOR2.10, U$8.10, U$8.11
unnamed: MOTOR2.11, MOTOR2.12, MOTOR2.13, MOTOR2.14, U$8.8, U$8.9
unnamed: MOTOR2.15, MOTOR2.16, MOTOR2.17, MOTOR2.18, U$8.6, U$8.7
unnamed: BB_CON.1, R20.2
unnamed: MOTOR2.20, U$8.4
unnamed: MOTOR2.19, U$8.3
unnamed: MOTOR2.21, U$8.2
unnamed: MOTOR2.23, U$8.1
unnamed: MOTOR1.7, MOTOR1.8, MOTOR1.9, MOTOR1.10, U$11.10, U$11.11
unnamed: MOTOR1.11, MOTOR1.12, MOTOR1.13, MOTOR1.14, U$11.8, U$11.9
unnamed: MOTOR1.15, MOTOR1.16, MOTOR1.17, MOTOR1.18, U$11.6, U$11.7
unnamed: MOTOR1.20, U$11.4
unnamed: MOTOR1.19, U$11.3
unnamed: MOTOR1.21, U$11.2
unnamed: MOTOR1.23, U$11.1
unnamed: MOTOR3.7, MOTOR3.8, MOTOR3.9, MOTOR3.10, U$9.10, U$9.11
unnamed: MOTOR3.11, MOTOR3.12, MOTOR3.13, MOTOR3.14, U$9.8, U$9.9
unnamed: MOTOR3.15, MOTOR3.16, MOTOR3.17, MOTOR3.18, U$9.6, U$9.7
unnamed: MOTOR3.20, U$9.4
unnamed: MOTOR3.19, U$9.3
unnamed: MOTOR3.21, U$9.2
unnamed: MOTOR3.23, U$9.1
unnamed: MOTOR4.7, MOTOR4.8, MOTOR4.9, MOTOR4.10, U$10.10, U$10.11
unnamed: MOTOR4.11, MOTOR4.12, MOTOR4.13, MOTOR4.14, U$10.8, U$10.9
unnamed: MOTOR4.15, MOTOR4.16, MOTOR4.17, MOTOR4.18, U$10.6, U$10.7
unnamed: MOTOR4.20, U$10.4
unnamed: MOTOR4.19, U$10.3
unnamed: MOTOR4.21, U$10.2
unnamed: MOTOR4.23, U$10.1
SCK: COM_BOARD.28, MOTOR1.29, MOTOR2.29, MOTOR3.29, MOTOR4.29
SS1: COM_BOARD.20, MOTOR1.31
SS2: COM_BOARD.22, MOTOR2.31
SS3: COM_BOARD.24, MOTOR3.31
SS4: COM_BOARD.26, MOTOR4.31
TO_DRIB: DRIB.2, DRIB_TRAN.DRAIN (D)
TO_NEON: NEON.1, R24.1
TRANS_OUT: CHARGE_D.A, U$3.P$1
UNBUF_DIVCAP: CAP_SENSE_BUF.3 (+IN), CLAMP1.A, CLAMP2.C, R14.1, R15.2

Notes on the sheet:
scale 250v -> 2.47v
To kick at different speeds without planning it in advance, we always start fully charged, but then stop the kick once our voltage has fallen by a certain amount. delta Voltage ~ Velocity.
reference voltage -> comparator AND kick_enable -> opto isolators -> transistor -> KICK!
add 100k pullup to 3.3v on micro board, or use internal pullup for done
Neon Indicator light to show when the Caps are charged and dangerous
to Microcontroller
threshold = 50% of xref
same radius, but shorter than old caps
Discharge Circuitry
capacitor sense circuitry
15v -> 3v division to measure battery voltage
max gate threshold: 2.6V. should turn on fine with 3.3!
Breakbeam output: 1.3v drop, 100mA. 2V / 20 ohm = 100mA
solenoid
DISCHARGE
IXTA3N50D2
ZTX718
***need to tune these resistors***
depletion mode
NO SSR

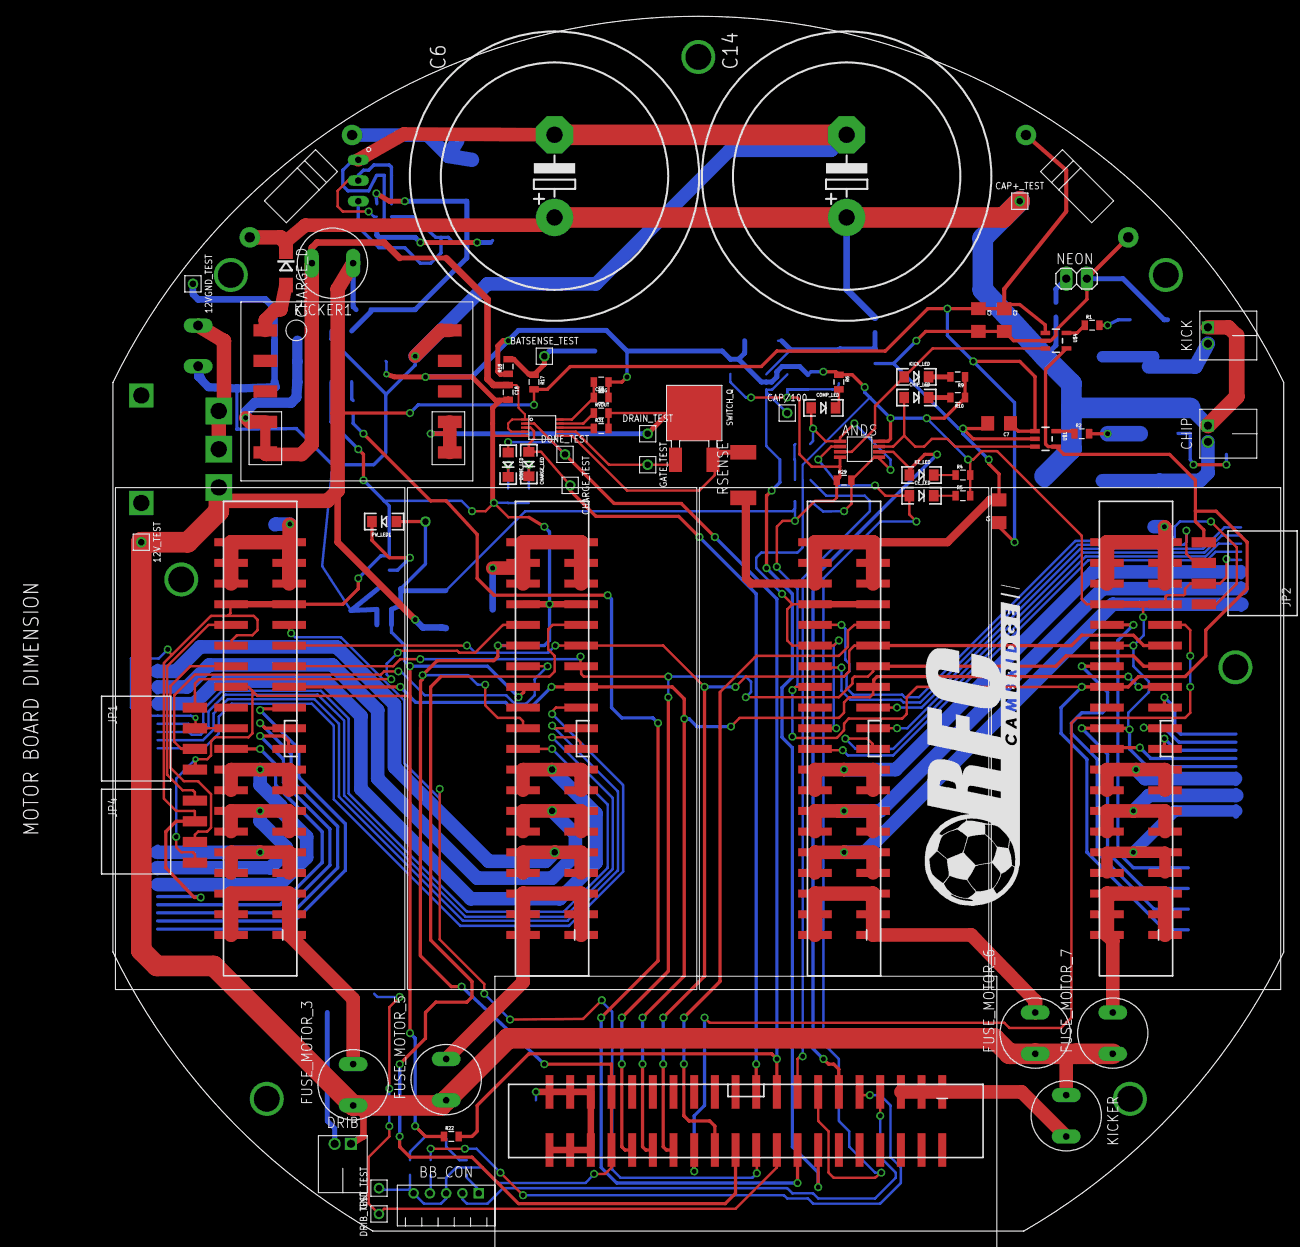
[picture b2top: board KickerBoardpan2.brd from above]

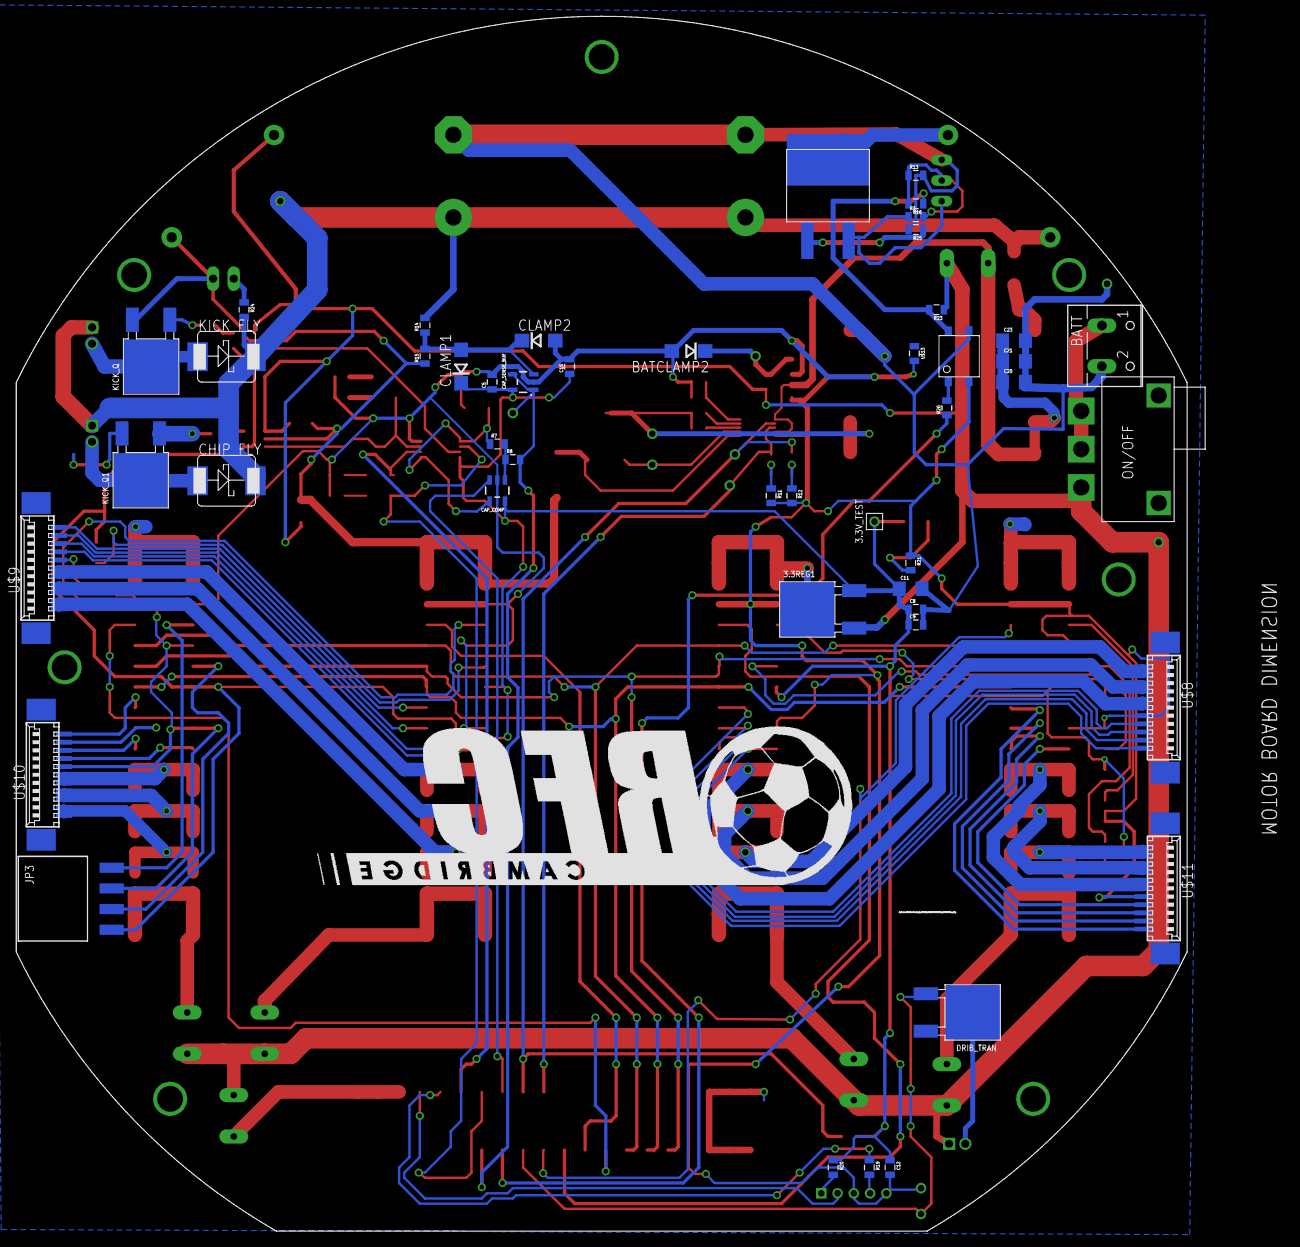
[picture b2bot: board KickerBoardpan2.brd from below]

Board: 2 copper layers, 143.9 x 149.3 mm, 119 parts (47 on the bottom side), 102 nets.

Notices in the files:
parts and their libraries:
SparkFun-Capacitors: Licensing: Creative Commons ShareAlike 4.0 International - https://creativecommons.org/licenses/by-sa/4.0
SparkFun-Aesthetics: Released under the Creative Commons Attribution Share-Alike 4.0 License
SparkFun-Aesthetics: https://creativecommons.org/licenses/by-sa/4.0
